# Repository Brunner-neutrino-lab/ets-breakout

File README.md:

# ETS per-channel SiPM breakout boards

Passive break-out boards that replace the (broken) **`iv-pulse-mux`** board in the
Brunner-lab **ETS-96-channel-IV-pulse-mux** system. Instead of relay-multiplexing 24
channels onto one shared sense line, each breakout board brings **every channel out to
its own coaxial jack** so channels can be biased/measured individually with external
instruments.

> Note: the public GitHub repo `IV-MUX-public` is a *different, older* board (15
> ch/board relay mux). The authoritative source is the read-only upstream snapshot
> under [`reference/ETS-96-channel-IV-pulse-mux/`](reference/) (`iv-pulse-mux`,
> connector **J5**) — see [`reference/UPSTREAM.md`](reference/UPSTREAM.md).

## What each board does

- Mates the detector-side connector **`QSE-040-01-L-D-A`** (J5) — same socket the
  `iv-pulse-mux` board used, mating the existing QTE-040 header upstream. **J5 sits on
  the back face (B.Cu)**, opposite the jacks: the detector plugs into the back, cables
  come off the front.
- Fans **25 signals → 25 coax jacks**: `SIPM_K0…K23` (24) + `IV` (1).
  `IV` is bussed on QSE pins 40 & 42 → one jack. `THERM4/THERM5` are **not** broken out.
  The detector socket keeps designator **J5** (upstream mapping); the jacks are **J6…J30**
  (K0→J6 … K23→J29, IV→J30), and each jack carries its channel identity (`K0…K23`, `IV`) as a
  **silkscreen label**. Mounting-hole designators (MH…) are hidden on silk.
- `GNDA` (52 signal-row pins + 8 G-pads) forms the ground/shield; a **guard ring** per
  channel tied to `GNDA`. No bias-tee / ESD diode / DC block.

### Variants
| Board | Jacks |
|-------|-------|
| **A** | 25 × MCX (straight, vertical through-hole) |
| **B** | 25 × SMA |
| **C** | 25 × U.FL |
| **D** | 25 × SMP (vertical SMT, SMP-MSLD-PCS-20) |

One board services one QSE-040 (25 ch). The full 96-channel system uses **4 boards**;
all four connectors share the identical J5 pinout, so a single layout works in every
position.

## Design decisions (2026-06-16)

| Aspect | Decision |
|--------|----------|
| Mechanical | **Free-form standalone** — only the QSE-040 must mate; fresh outline + mounting, no size constraint |
| J5 mounting face | **Back (B.Cu)** — detector mates on the back, all coax jacks on the front |
| Jack mounting | **Edge / right-angle** — jacks at board edges, cables exit sideways |
| Signal integrity | **Controlled 50 Ω, 4-layer** (L1 sig / L2 GND / L3 GND / L4 sig) |
| Guard | Guard ring per channel → `GNDA` |

## Pinout = single source of truth

[`pinout.py`](pinout.py) holds the authoritative QSE-040 (J5) pin→net map, derived from
the upstream schematic netlist (`kicad-cli sch export netlist`), **not** hand-transcribed
from a screenshot. The generator imports it; never hand-place a channel. Re-export and
regenerate if the upstream board changes.

```
python pinout.py             # dump signal -> QSE pin map
python tests/test_pinout.py  # sanity + self-consistency checks
```

## Build pipeline

All `tools/*.py` run under KiCad's bundled interpreter
(`"C:/Program Files/KiCad/10.0/bin/python.exe"`).

```
# Board A (MCX, through-hole) — FreeRouting autoroute, ZERO signal vias:
tools/gen_board.py mcx                 # placement + nets + outline + holes (balanced ~12/13 split; SPLIT="planar" = old 8/16)
tools/finalize_board.py <pcb> setup    # 4-layer stackup + GND zones (no routes yet)
tools/export_dsn.py <pcb> B.Cu         # write Specctra .dsn for the router
#   -> FreeRouting v2.2.4 (java) autoroute -> .ses
tools/import_ses.py <pcb>              # pull the routed B.Cu tracks back in
tools/finalize_board.py <pcb> stitch   # GND stitching vias
tools/fill_zones.py <pcb>              # fill GND pours (separate pass)
tools/tie_islands.py <pcb>             # island-tie vias
kicad-cli pcb drc <pcb>                # verify (0 violations, 0 unconnected)

# Boards B/C/D (SMA/U.FL/SMP) — deterministic router, single finalize pass:
tools/gen_board.py [sma|ufl|smp]
tools/finalize_board.py <pcb>          # stackup + 50 ohm routes + GND zones + stitching (one pass)
tools/fill_zones.py <pcb>
kicad-cli pcb drc <pcb>

kicad-cli pcb export gerbers|drill|pos ... ; tools/make_bom.py <pcb> <csv>   # fab outputs
```

**Board A** routes as a **balanced ~12/13 planar fan on B.Cu** (engineer-reviewed). The 25
jacks are split 12 on the west edge / 13 on the east and **ordered by their QSE pin** so every
native channel escapes as a **straight line**: west = K8–K15 (native) + K16,K17 (wrapping the
top corner) + K6,K7 (wrapping the bottom corner); east = K18–K23, IV, K0–K5. The 4 spilled
channels **wrap around the connector ends on B.Cu** (2 per corner), so the fan stays **all-B.Cu
with zero connector crossings and zero signal vias** (the through-hole MCX signal pin is plated
through every layer, so the B.Cu escape lands on it with no face-change via). FreeRouting does
the autoroute; only GND stitching + island-tie vias remain. Balancing shrank the board 32 mm
(75 × 157 → **75.0 × 125.2 mm**). The old lopsided 8/16 fan is retained as the `gen_board`
`SPLIT="planar"` option; `SPLIT="balanced"` is the default. **Boards B/C/D** still use the
deterministic router — escape past the QSE pads → one straight diagonal to the jack → straight
into the signal pad between grounds — with a 12/12 split (the `SPLIT="balanced"` flag) that
crosses 4 channels on the bottom layer. Vertical jacks (U.FL, MCX, SMP) are auto-rotated so
their signal pad faces the QSE.

## Status

**All four boards route DRC-clean (0 violations, 0 unconnected)** at the 50 Ω trace
width on the JLCPCB **JLC04161H-7628** 4-layer 1.6 mm stackup. Board A carries **0 signal
vias** (GND stitching + island-tie vias only; all 25 nets on B.Cu).

| Board | Connector | Size | Fab package |
|-------|-----------|------|-------------|
| A | MCX straight, through-hole (MCX-J-P-H-ST-TH1) | 75.0 × 125.2 mm | `boards/board-A-mcx/board-A-mcx-fab.zip` |
| B | SMA (901-143-6RFX) | 75 × 149 mm | `boards/board-B-sma/board-B-sma-fab.zip` |
| C | U.FL (U.FL-R-SMT-1) | 70 × 99 mm | `boards/board-C-ufl/board-C-ufl-fab.zip` |
| D | SMP (SMP-MSLD-PCS-20) | 75 × 120 mm | `boards/board-D-smp/board-D-smp-fab.zip` |

Each fab zip = gerbers (4 copper + mask/silk/edge) + Excellon drill + position CSV + BOM CSV.

**Assembly:** the default build is **fab-only + hand-solder** (exact Samtec parts from
DigiKey). An optional **JLCPCB assembled build is possible** as a mixed SMT (QSE) + THT (MCX)
job using LCSC parts: QSE-040 = **C3652741** (exact Samtec, plain -A), MCX = **C5137197**
(BAT Wireless `BWMCX-KE`, a generic 50 Ω THT MCX jack; alt **C49118404**). Both are JLC-library
*Extended* parts and the 25 THT MCX jacks need JLC's through-hole/wave-solder assembly add-on.
**Gate before an assembled order:** confirm the `BWMCX-KE` land pattern matches our footprint
(centre signal + 4 grounds on 5.08 mm, drills 1.10/1.40) — it's a generic equivalent, not
dimensionally verified. The fab BOM (`make_bom.py`) carries these in an **LCSC column**. Fab is
**JLCPCB only**.

**Impedance:** channel traces are **0.325 mm** wide (unchanged) ≈ 50 Ω single-ended microstrip
on the JLCPCB **JLC04161H-7628** 4-layer 1.6 mm stack (0.2104 mm 7628 prepreg to the adjacent
inner GND plane, Dk ≈ 4.4), GND pour held back 0.30 mm to limit coplanar coupling. 0.325 mm is
JLC's own published 50 Ω single-ended width for JLC04161H-7628; the full derivation (JLCPCB
calculator RS_50 = 0.3244 mm + KiCad TransLine / IPC-2141 microstrip, every input stated) is in
[`docs/impedance.md`](docs/impedance.md). **Order as controlled impedance** (JLC's
impedance-control option on that stackup) so JLC re-tunes the etched width to their exact stackup.

**Footprints — all datasheet-verified:** MCX `Samtec_MCX-J-P-H-ST-TH1` (straight, vertical
**through-hole** jack) matches the Samtec drawing (`docs/datasheets/`, mcx-j-p-x-st-th1-mkt):
pad 1 signal drill Ø1.10 mm centered + 4× ground drill Ø1.40 mm on a 5.08 mm square. SMA and
U.FL from the KiCad library; QSE-040 from the ETS repo; SMP `SMP_Amphenol_SMP-MSLD-PCS-20`
(Amphenol RF, vertical SMT) is the SnapMagic land pattern (pad `G` renamed to `2`), signal on
an external tab.

**3D models:** QSE-040 and SMP have local STEP models in [`models/`](models/); U.FL uses
KiCad's bundled model. SMA and the through-hole MCX have no 3D model yet (gap). Models are
visual only — fab is unaffected.

**Before committing to fab:**
- Boards are built directly from `pinout.py` (no netlist-driven flow). A **reference
  schematic for human review** is in [`docs/schematic/`](docs/schematic/) (PDF + `.kicad_sch`),
  generated from the same `pinout.py` by `tools/gen_schematic.py` — its exported netlist is
  verified identical to the pin map.
- ~~Confirm the straight-MCX orderable MPN~~ **Confirmed 2026-07-15:** Board A is now
  **through-hole** — `MCX-J-P-H-ST-TH1` (DigiKey SAM8944-ND). Purchase package in [`order/`](order/).

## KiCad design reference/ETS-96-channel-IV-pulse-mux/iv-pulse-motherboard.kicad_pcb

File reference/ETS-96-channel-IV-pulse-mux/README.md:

# ETS 96-Channel IV-Pulse Multiplexer

**Organization:** McGill University Physics – Electronic Design Support Group  
**Designer:** Eamon Egan  
**Schematic Date:** 2019-11-12 (Rev 1.0)  
**Design Tool:** KiCad 9.0  

---

## Overview

This repository contains the complete design files for a **96-channel I-V curve pulse multiplexer** used in detector physics instrumentation. The system routes bias voltage and sense signals to one of 96 detector channels (e.g., SiPMs or similar devices) under Arduino microcontroller command, enabling automated current-voltage (I-V) characterization of large detector arrays.

The system is organized as:
- **Four 24-channel Mux boards** (`iv-pulse-mux`) — each handling 24 detector channels via reed relays and shift registers.
- **One Motherboard** (`iv-pulse-motherboard`) — orchestrating all four mux boards, distributing power, and providing the interface to the control system.
- **Arduino firmware** (`Arduino code/iv-mux/iv-mux.ino`) — running on an Arduino Nano Every (ATmega4809), accepting serial commands to switch channels, read temperature, and control auxiliary lines.

---

## Repository Layout

```
.
├── README.md                          ← This file
├── docs/                              ← Project documentation
│   ├── architecture.md                ← System-level design overview
│   ├── hardware/
│   │   ├── iv-pulse-mux-board.md      ← IV Pulse Mux PCB documentation
│   │   ├── motherboard.md             ← Motherboard documentation
│   │   ├── component-libraries.md     ← Custom schematic and footprint libraries
│   │   └── pcb-design-rules.md        ← Net classes and PCB design rules
│   ├── firmware/
│   │   ├── firmware-overview.md       ← Arduino firmware architecture
│   │   └── serial-commands.md         ← Serial command protocol reference
│   ├── fabrication/
│   │   └── fabrication-guide.md       ← Fabrication and assembly guide
│   └── operation/
│       └── user-guide.md              ← System operation and integration guide
│
├── Arduino code/iv-mux/iv-mux.ino    ← Microcontroller firmware
│
├── iv-pulse-mux.kicad_pro             ← KiCad project: IV Pulse Mux board
├── iv-pulse-mux.kicad_sch             ← Root schematic (IV Pulse Mux)
├── iv-pulse-mux.kicad_pcb             ← PCB layout (IV Pulse Mux)
│
├── iv-pulse-motherboard.kicad_pro     ← KiCad project: Motherboard
├── iv-pulse-motherboard.kicad_sch     ← Root schematic (Motherboard)
├── iv-pulse-motherboard.kicad_pcb     ← PCB layout (Motherboard)
│
├── Channels.kicad_sch                 ← Hierarchical sheet: 24 channel cells
├── sense-relay.kicad_sch              ← Hierarchical sheet: single sense relay cell
├── sense-relays.kicad_sch             ← Hierarchical sheet: sense relay group
├── bias-relay.kicad_sch               ← Hierarchical sheet: single bias relay cell
├── bias-relays-with-control.kicad_sch ← Hierarchical sheet: bias relay group
├── control.kicad_sch                  ← Hierarchical sheet: shift register control
├── muxboard-interface.kicad_sch       ← Hierarchical sheet: board connector interface
│
├── iv-mux.pretty/                     ← Custom PCB footprint library
├── samtec-footprints.pretty/          ← Samtec QSE connector footprints
├── passthrough.pretty/                ← Panel passthrough connector footprints
├── bias-switches-symlibs/             ← Custom schematic symbol library
│
├── fab-files.kicad_jobset             ← Automated fabrication output job set
├── fabrication-toolkit-options.json   ← Gerber export settings
├── fp-lib-table                       ← KiCad footprint library table
├── sym-lib-table                      ← KiCad symbol library table
└── mcgill-university-2.*              ← McGill University logo (SVG/DXF/PNG)
```

---

## Quick-Start

### Hardware

1. Order PCBs and assemble using the [Fabrication Guide](docs/fabrication/fabrication-guide.md).
2. Stack up to four Mux boards on the Motherboard via the Samtec QSE-040 connectors.
3. Connect detector channels to MCX connectors on the Mux boards.
4. Apply bias supply and sense lines via the Motherboard.

### Firmware

1. Open `Arduino code/iv-mux/iv-mux.ino` in the Arduino IDE.
2. Ensure `#define IVPULSEMUX` is present (enabled by default).
3. Select board: **Arduino Mega or Mega 2560** (required for ATmega4809 / Nano Every with Mega2560 profile).
4. Upload to the Arduino Nano Every.
5. Open a serial terminal at **9600 baud**.
6. Type a blank line to print the command help.

For a full command reference, see the [Serial Commands Reference](docs/firmware/serial-commands.md).

---

## Documentation Index

| Document | Description |
|---|---|
| [System Architecture](docs/architecture.md) | Top-level design intent, block diagram, and signal flow |
| [IV Pulse Mux Board](docs/hardware/iv-pulse-mux-board.md) | Schematic, PCB, and component details for the 24-channel mux board |
| [Motherboard](docs/hardware/motherboard.md) | Schematic and PCB details for the control motherboard |
| [Component Libraries](docs/hardware/component-libraries.md) | Custom schematic symbols and PCB footprints |
| [PCB Design Rules](docs/hardware/pcb-design-rules.md) | Net classes, clearances, and trace width rules |
| [Firmware Overview](docs/firmware/firmware-overview.md) | Arduino firmware architecture and state machine |
| [Serial Commands](docs/firmware/serial-commands.md) | Complete serial command protocol reference |
| [Fabrication Guide](docs/fabrication/fabrication-guide.md) | PCB fab, BOM, and assembly instructions |
| [User / Operation Guide](docs/operation/user-guide.md) | How to operate and integrate the system |

---

## Known Issues / Open Items (Rev 1.0)

- `BYPASS` signal is connected to Arduino pin 12 as a **temporary workaround**; the comment in firmware notes this should be corrected in a future revision.
- The `iv_on_pins[]` array uses analog pins `A0–A3` instead of the originally intended `THERM1–THERM4` thermistor pins — firmware comment notes this was an oversight.
- Low-power sleep mode (`LOWPOWER_SLEEP`) was prototyped but **is currently disabled**; register access issues on the ATmega4809 need to be resolved.
- The `q` (sequence) command is **only available in non-IV-pulse-mux mode** (i.e., the older 6×15 channel variant).
- Symbol library `iv-mux-rescue` references an absolute path on the designer's machine (`C:/Users/eamon/...`) and must be remapped when opening on a different workstation.

---

## Revision History

| Rev | Date | Description |
|---|---|---|
| 1.0 | 2019-11-12 | Initial release (schematic date) |

---

## License

Hardware design files are the property of McGill University Physics, Electronic Design Support Group. Contact the Brunner Neutrino Lab for use and distribution terms.

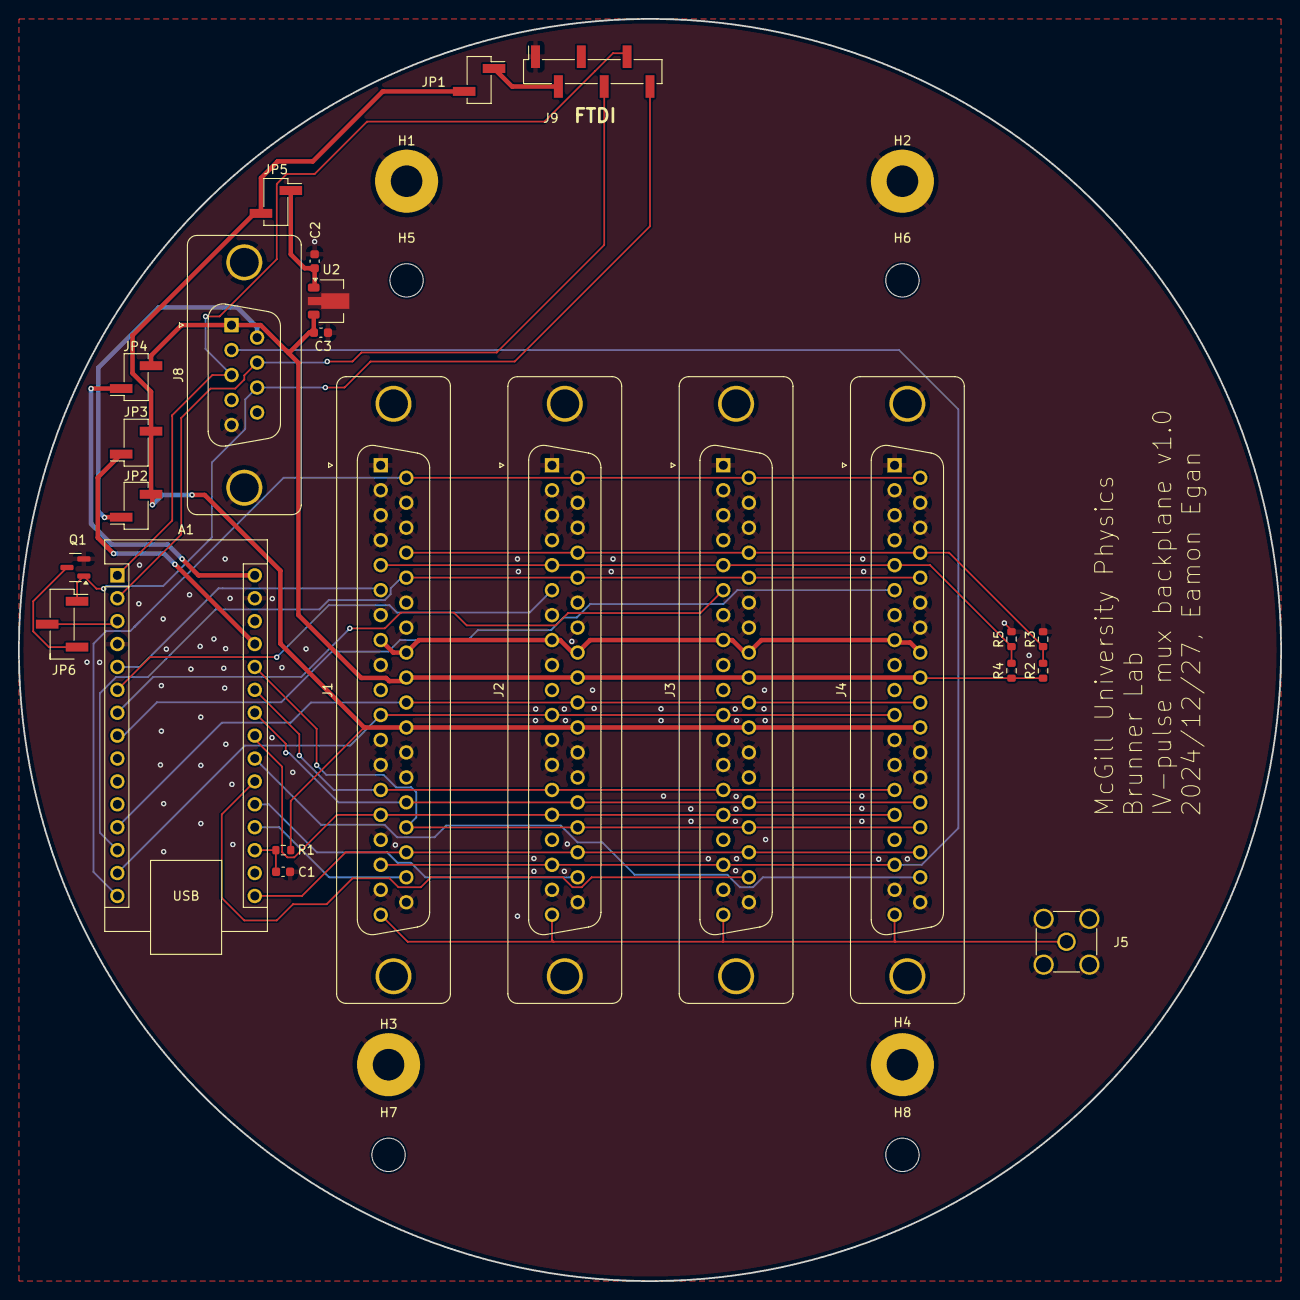
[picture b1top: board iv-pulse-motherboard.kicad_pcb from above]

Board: 2 copper layers, 140.0 x 140.0 mm, 32 parts (0 on the bottom side), 36 nets.

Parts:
A1: Arduino_Nano_Every; Arduino_Nano
C1, C2, C3: C; C_0603_1608Metric
H1, H2, H3, H4: MountingHole_Pad; MountingHole_3.5mm_Pad
H5, H6, H7, H8: MountingHole; MountingHole_3.7mm
J1, J2, J3, J4: DC37_Receptacle_MountingHoles; DSUB-37_Female_Vertical_P2.77x2.84mm_MountingHoles
J5: Conn_Coaxial; SMA_Amphenol_901-144_Vertical
J8: DE9_Receptacle_MountingHoles; DSUB-9_Female_Vertical_P2.77x2.84mm_MountingHoles
J9: Conn_01x06; PinHeader_1x06_P2.54mm_Vertical_SMD_Pin1Right
JP1, JP2, JP3, JP4, JP5: Jumper_2_Open; PinHeader_1x02_P2.54mm_Vertical_SMD_Pin1Right
JP6: Jumper_3_Open; PinHeader_1x03_P2.54mm_Vertical_SMD_Pin1Right
Q1: 2N7002; SOT-23
R1, R2, R3, R4, R5: R_US; R_0603_1608Metric
U2: L78L05_SOT89; SOT-89-3

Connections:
+5V: J1.30, J2.30, J3.30, J4.30, JP1.2 (B), JP2.2 (B), JP3.2 (B), JP5.2 (B), R1.1
+12V: C3.1, J1.28, J2.28, J3.28, J4.28, J8.1, JP4.2 (B), R2.1, R4.1, U2.3 (IN)
/FTDI_RTS: J8.8, J9.6, JP6.1 (A), Q1.1 (G)
/FTDI_RXD: A1.1 (TX1), J8.3, J9.5
/FTDI_TXD: A1.2 (RX1), J8.7, J9.4
/Mux Boards/BYPASS: A1.15 (MISO/D12), J1.20, J2.20, J3.20, J4.20
/Mux Boards/IV_ON: A1.16 (SCK/D13), J1.35, J2.35, J3.35, J4.35
/Mux Boards/IV_OUT: J1.19, J2.19, J3.19, J4.19, J5.1 (In)
/Mux Boards/PIN_BIAS1: J1.23, J2.23, J3.23, J4.23, R2.2, R3.1
/Mux Boards/PIN_BIAS2: J1.5, J2.5, J3.5, J4.5, R4.2, R5.1
/Mux Boards/RCLK: A1.13 (D10), J1.24, J2.24, J3.24, J4.24
/Mux Boards/SER_IN_1: A1.5 (D2), J1.6
/Mux Boards/SER_IN_2: A1.6 (D3), J2.6
/Mux Boards/SER_IN_3: A1.7 (D4), J3.6
/Mux Boards/SER_IN_4: A1.8 (D5), J4.6
/Mux Boards/SRCLK: A1.12 (D9), J1.29, J2.29, J3.29, J4.29
/Mux Boards/VB_POS: J1.17, J2.17, J3.17, J4.17, J8.2
/Mux Boards/~OE: A1.14 (MOSI/D11), J1.11, J2.11, J3.11, J4.11
/THERM1: A1.19 (A0), J1.36
/THERM2: A1.20 (A1), J2.36
/THERM3: A1.21 (A2), J3.36
/THERM4: A1.22 (A3), J4.36
/THERMSEL0: A1.23 (SDA/A4), J1.15, J2.15, J3.15, J4.15
/THERMSEL1: A1.24 (SCL/A5), J1.33, J2.33, J3.33, J4.33
/THERMSEL2: A1.25 (A6), J1.14, J2.14, J3.14, J4.14
/THERM_ON: A1.26 (A7), J1.34, J2.34, J3.34, J4.34
GNDA: A1.4 (GND), A1.29 (GND), C1.1, C2.2, C3.2, H1.1, H2.1, H3.1, H4.1, J1.0 (PAD), J1.1, J1.2, J1.3, J1.4, J1.7, J1.9, J1.12, J1.13, J1.16, J1.18, J1.21, J1.22, J1.25, J1.26, J1.31, J1.32, J1.37, J2.0 (PAD), J2.1, J2.2, J2.3, J2.4, J2.7, J2.9, J2.12, J2.13, J2.16, J2.18, J2.21, J2.22, J2.25, J2.26, J2.31, J2.32, J2.37, J3.0 (PAD), J3.1, J3.2, J3.3, J3.4, J3.7, J3.9, J3.12, J3.13, J3.16, J3.18, J3.21, J3.22, J3.25, J3.26, J3.31, J3.32, J3.37, J4.0 (PAD), J4.1, J4.2, J4.3, J4.4, J4.7, J4.9, J4.12, J4.13, J4.16, J4.18, J4.21, J4.22, J4.25, J4.26, J4.31, J4.32, J4.37, J5.2 (Ext), J8.0 (PAD), J8.5, J9.1, Q1.2 (S), R3.2, R5.2, U2.2 (GND)
GNDD: J1.8, J1.27, J2.8, J2.27, J3.8, J3.27, J4.8, J4.27
unnamed: A1.27 (+5V), JP3.1 (A)
unnamed: A1.18 (AREF), C1.2, R1.2
unnamed: A1.30 (VIN), JP4.1 (A)
unnamed: J9.2, JP1.1 (A)
unnamed: J8.6, JP2.1 (A)
unnamed: C2.1, JP5.1 (A), U2.1 (OUT)
unnamed: JP6.3 (B), Q1.3 (D)
unnamed: A1.3 (~RESET), JP6.2 (C)

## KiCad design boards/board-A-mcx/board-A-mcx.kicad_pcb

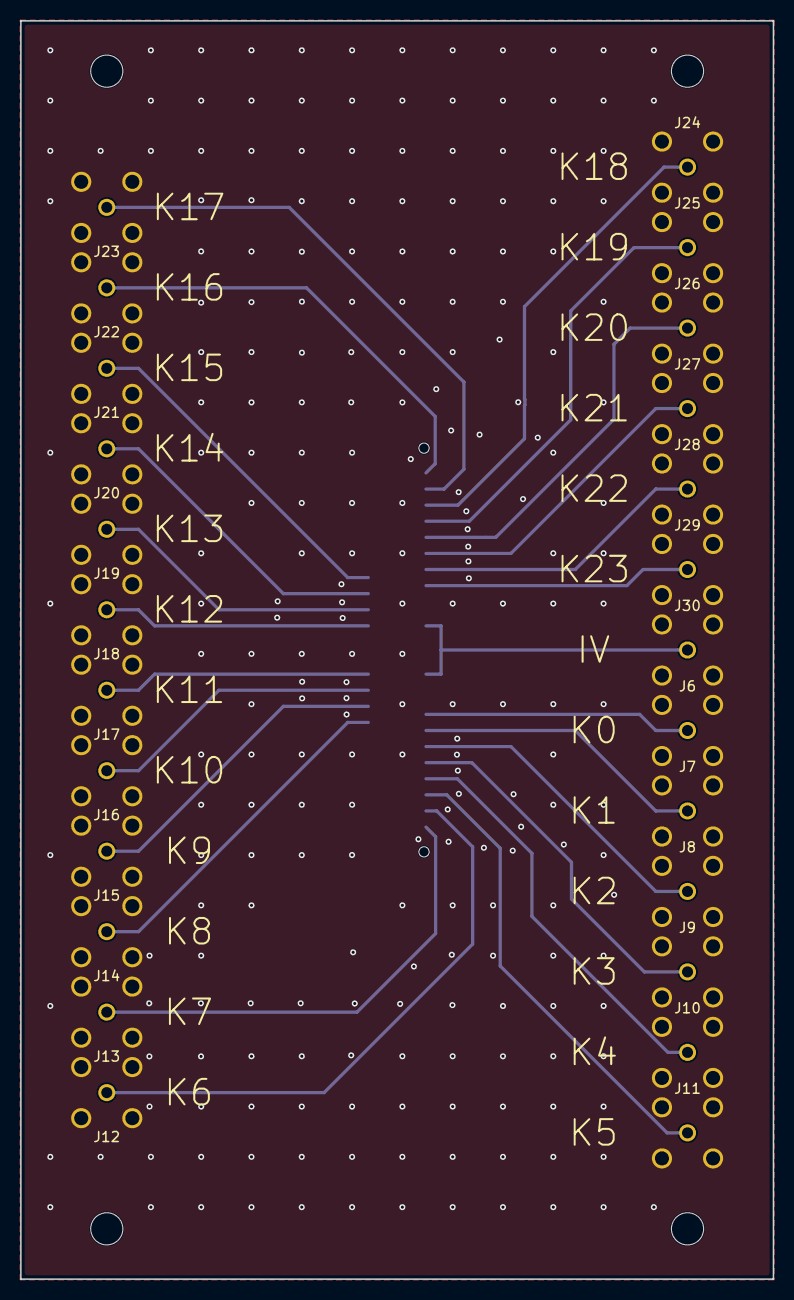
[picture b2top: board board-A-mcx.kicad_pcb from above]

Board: 4 copper layers, 74.8 x 125.1 mm, 30 parts (1 on the bottom side), 26 nets.

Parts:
J5: SAMTEC_QSE-040-01-X-D-A
J6, J7, J8, J9, J10, J11, J12, J13, J14, J15, J16, J17, J18, J19, J20, J21, J22, J23, J24, J25, J26, J27, J28, J29, J30: Samtec_MCX-J-P-H-ST-TH1
MH1, MH2, MH3, MH4: MountingHole_3.2mm_M3

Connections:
GNDA: J5.01, J5.03, J5.04, J5.05, J5.07, J5.08, J5.09, J5.11, J5.12, J5.13, J5.15, J5.16, J5.17, J5.19, J5.20, J5.21, J5.23, J5.24, J5.25, J5.28, J5.29, J5.32, J5.33, J5.34, J5.36, J5.37, J5.38, J5.43, J5.44, J5.46, J5.47, J5.48, J5.50, J5.51, J5.54, J5.55, J5.57, J5.58, J5.59, J5.61, J5.62, J5.63, J5.65, J5.66, J5.67, J5.69, J5.70, J5.71, J5.73, J5.74, J5.75, J5.78, J5.G1, J5.G2, J5.G3, J5.G4, J5.G5, J5.G6, J5.G7, J5.G8, J6.2, J7.2, J8.2, J9.2, J10.2, J11.2, J12.2, J13.2, J14.2, J15.2, J16.2, J17.2, J18.2, J19.2, J20.2, J21.2, J22.2, J23.2, J24.2, J25.2, J26.2, J27.2, J28.2, J29.2, J30.2
IV: J5.40, J5.42, J30.1
SIPM_K0: J5.30, J6.1
SIPM_K1: J5.26, J7.1
SIPM_K2: J5.22, J8.1
SIPM_K3: J5.18, J9.1
SIPM_K4: J5.14, J10.1
SIPM_K5: J5.10, J11.1
SIPM_K6: J5.06, J12.1
SIPM_K7: J5.02, J13.1
SIPM_K8: J5.27, J14.1
SIPM_K9: J5.31, J15.1
SIPM_K10: J5.35, J16.1
SIPM_K11: J5.39, J17.1
SIPM_K12: J5.41, J18.1
SIPM_K13: J5.45, J19.1
SIPM_K14: J5.49, J20.1
SIPM_K15: J5.53, J21.1
SIPM_K16: J5.80, J22.1
SIPM_K17: J5.76, J23.1
SIPM_K18: J5.72, J24.1
SIPM_K19: J5.68, J25.1
SIPM_K20: J5.64, J26.1
SIPM_K21: J5.60, J27.1
SIPM_K22: J5.56, J28.1
SIPM_K23: J5.52, J29.1

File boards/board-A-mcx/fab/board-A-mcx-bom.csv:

Designators,Qty,Description,Manufacturer,MPN,Digi-Key,LCSC,KiCad Footprint
"J10, J11, J12, J13, J14, J15, J16, J17, J18, J19, J20, J21, J22, J23, J24, J25, J26, J27, J28, J29, J30, J6, J7, J8, J9",25,"MCX jack, straight (vertical) through-hole, 50 ohm",Samtec,MCX-J-P-H-ST-TH1,SAM8944-ND,C5137197 (BWMCX-KE equiv; confirm footprint),Samtec_MCX-J-P-H-ST-TH1
"MH1, MH2, MH3, MH4",4,"M3 mounting hole, non-plated",,,,,MountingHole_3.2mm_M3
J5,1,QSE-040 board-to-board socket (mates detector QTE-040),Samtec,QSE-040-01-L-D-A,SAM8124-ND,C3652741,SAMTEC_QSE-040-01-X-D-A

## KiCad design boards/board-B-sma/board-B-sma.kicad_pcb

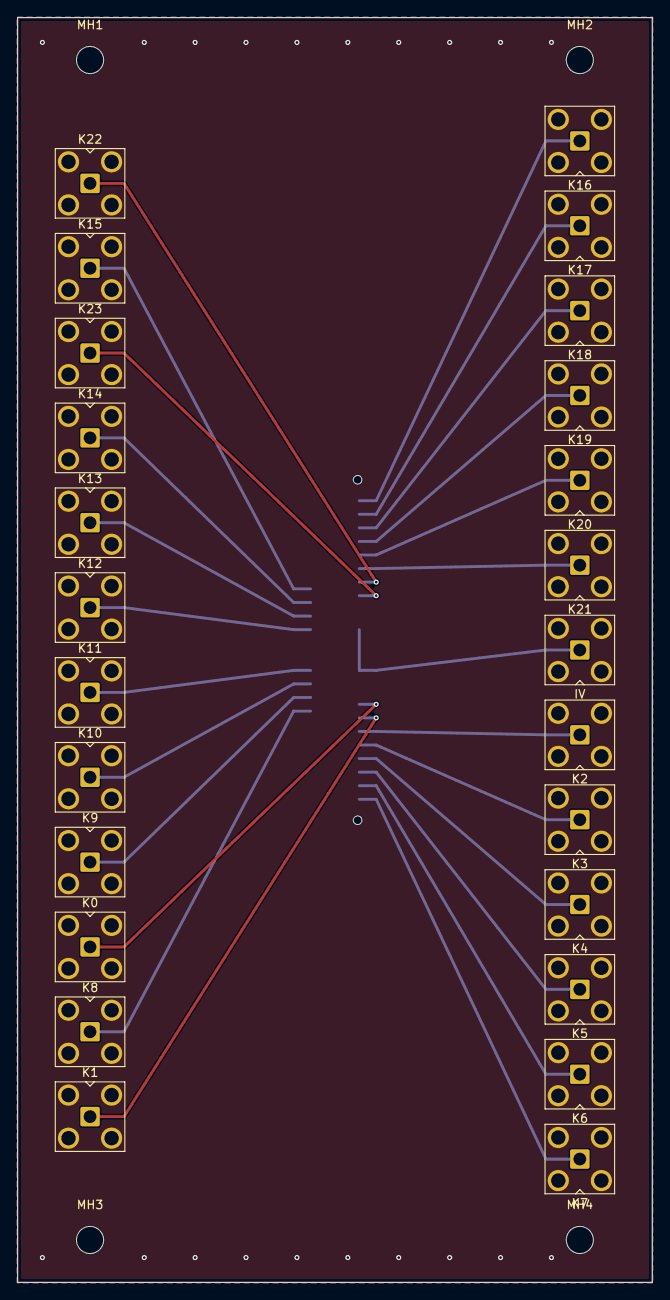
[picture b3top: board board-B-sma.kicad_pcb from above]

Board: 4 copper layers, 74.8 x 149.1 mm, 30 parts (1 on the bottom side), 26 nets.

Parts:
IV: SMA_Amphenol_901-143_Horizontal
J5: SAMTEC_QSE-040-01-X-D-A
K0, K1, K2, K3, K4, K5, K6, K7, K8, K9, K10, K11, K12, K13, K14, K15, K16, K17, K18, K19, K20, K21, K22, K23: SMA_Amphenol_901-143_Horizontal
MH1, MH2, MH3, MH4: MountingHole_3.2mm_M3

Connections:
GNDA: IV.2, J5.01, J5.03, J5.04, J5.05, J5.07, J5.08, J5.09, J5.11, J5.12, J5.13, J5.15, J5.16, J5.17, J5.19, J5.20, J5.21, J5.23, J5.24, J5.25, J5.28, J5.29, J5.32, J5.33, J5.34, J5.36, J5.37, J5.38, J5.43, J5.44, J5.46, J5.47, J5.48, J5.50, J5.51, J5.54, J5.55, J5.57, J5.58, J5.59, J5.61, J5.62, J5.63, J5.65, J5.66, J5.67, J5.69, J5.70, J5.71, J5.73, J5.74, J5.75, J5.78, J5.G1, J5.G2, J5.G3, J5.G4, J5.G5, J5.G6, J5.G7, J5.G8, K0.2, K1.2, K2.2, K3.2, K4.2, K5.2, K6.2, K7.2, K8.2, K9.2, K10.2, K11.2, K12.2, K13.2, K14.2, K15.2, K16.2, K17.2, K18.2, K19.2, K20.2, K21.2, K22.2, K23.2
IV: IV.1, J5.40, J5.42
SIPM_K0: J5.30, K0.1
SIPM_K1: J5.26, K1.1
SIPM_K2: J5.22, K2.1
SIPM_K3: J5.18, K3.1
SIPM_K4: J5.14, K4.1
SIPM_K5: J5.10, K5.1
SIPM_K6: J5.06, K6.1
SIPM_K7: J5.02, K7.1
SIPM_K8: J5.27, K8.1
SIPM_K9: J5.31, K9.1
SIPM_K10: J5.35, K10.1
SIPM_K11: J5.39, K11.1
SIPM_K12: J5.41, K12.1
SIPM_K13: J5.45, K13.1
SIPM_K14: J5.49, K14.1
SIPM_K15: J5.53, K15.1
SIPM_K16: J5.80, K16.1
SIPM_K17: J5.76, K17.1
SIPM_K18: J5.72, K18.1
SIPM_K19: J5.68, K19.1
SIPM_K20: J5.64, K20.1
SIPM_K21: J5.60, K21.1
SIPM_K22: J5.56, K22.1
SIPM_K23: J5.52, K23.1

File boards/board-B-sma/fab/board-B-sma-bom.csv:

Designators,Qty,Description,Manufacturer,MPN,Digi-Key,KiCad Footprint
"IV, K0, K1, K10, K11, K12, K13, K14, K15, K16, K17, K18, K19, K2, K20, K21, K22, K23, K3, K4, K5, K6, K7, K8, K9",25,"SMA jack, right-angle through-hole, 50 ohm",Amphenol RF,901-143-6RFX,ARFX1232-ND,SMA_Amphenol_901-143_Horizontal
"MH1, MH2, MH3, MH4",4,"M3 mounting hole, non-plated",,,,MountingHole_3.2mm_M3
J5,1,QSE-040 board-to-board socket (mates detector QTE-040),Samtec,QSE-040-01-L-D-A,,SAMTEC_QSE-040-01-X-D-A

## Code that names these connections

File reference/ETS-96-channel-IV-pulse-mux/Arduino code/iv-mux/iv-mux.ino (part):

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// This is a hack to make the motherboard V1.0 work to address more than one daughterboard
// By mistake, a single IV_ON was designated on the microcontroller, and distributed to all boards
// instead of 4 of them, one distributed to each of the boards.
// Instead we used THERM1 - THERM4, and bridged each THERMn to the respective IV_ON pin, on the motherboard 
// (and also cut the IV_ON trace tying them all together)
int iv_on_pins[boardCount] = { A0, A1, A2, A3 };  

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// Delete above version of iv_on_pins definition
//int iv_on_pins[boardCount] = { 6, 7, 8, 13 };  

const int SRCLK = 9;   // serial clock
const int RCLK = 10;   // strobe to active register
const int SRCLR = 11;  // asynchronous clear (active low)

//const int IV_ON = 13;  // DELETE ME
const int OE = 11;

const int BYPASS = 12;  // TEMPORARY - it shouldn't have been connected to pin 12!

#else

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
// shift register (74HC595) control pinout
int serPins[boardCount] = { 2, 3, 4, 5, 6, 7 };
const int SRCLK = 9;   // serial clock
const int RCLK = 10;   // strobe to active register
const int SRCLR = 11;  // asynchronous clear (active low)

#endif
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
// TEMPORARY
#ifdef IVPULSEMUX
  pinMode(BYPASS, OUTPUT);
  digitalWrite(BYPASS, LOW);
#endif

  pinMode(SRCLK, OUTPUT);
  pinMode(RCLK, OUTPUT);

#ifdef IVPULSEMUX
#else
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
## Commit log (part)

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2026-06-24 initial upload
